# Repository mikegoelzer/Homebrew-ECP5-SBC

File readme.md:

# Homebrew RISC-V Computer

This is the hardware repo for a homebrew "personal computer" designed from scratch down to the logic gate level.

The computer is based on [my custom RISC-V CPU core](https://github.com/mikegoelzer/riscv) (pipelined, in-order, 5-stage) and has all the common peripherals you'd expect on a PC circa the early-2000s like USB, HDMI, keyboard and mouse, etc.

This repo is focused specifically on the PCBs necessary to build the complete computer.

## Hardware

In this repo, you'll find all the Kicad files and bills of materials needed to construct the entire computer.  There are several PCBs:

- [Compute Module](./hardware/cm/readme.md). This is the heart of the computer:  an FPGA that implements the RISC-V CPU and some SDRAM that serves as the computer's main memory. It has two 100-pin Hirose DF13 snap-in connectors on the bottom, which mate with the motherboard.
- [Motherboard](./hardware/motherboard/readme.md). The Compute Module snaps into this motherboard, which breaks out the common PC periperal interfaces, like HDMI, VGA, JTAG, and more.  It also has an SD card to serve as the computer's "hard drive," a boot flash, and some diagnostic LEDs and switches.
- [Power Supply](./hardware/pd-booster-16amps/readme.md). Power initially comes into the motherboard via a USB-C cable.  Because I wanted to learn a bit about USB Power Deliver (USB-PD) as part of this project, I designed this plug-in board that negotiates higher voltages and currents and then buck-boost converts them to a stable 5V to power the motherboard.
- [Hat](./hardware/hat/readme.md).  This is a top board that sits above the motherboard on standoffs and provides a touch screen plus a smaller OLED display for debugging your Verilog.  The name is, of course, inspired by the Pi HAT, though it bears no electrical or mechanical resemblance.

## About this project

This project was a personal hobby exercise that I pursued on and off over a couple of years.  Everything is massively over-engineered because I was trying to maximize my learnings. 🤷‍♀️

## Acknowledgements

This hardware was heavily inspired by the [ULX3S](https://radiona.org/ulx3s/), which I consider the best low-cost Lattice ECP5 FPGA board ever created.

I also borrowed ideas from several other open-source ECP5 designs:

- [Lattice ECP5 Eval Board](https://www.latticesemi.com/products/developmentboardsandkits/ecp5evaluationboard)
- [Trellis Board](https://github.com/gatecat/TrellisBoard).  Not sure if this was ever sold to the public, but this guy's design is utterly brilliant.
- [Orange Crab](https://github.com/orangecrab-fpga/orangecrab-hardware)

## License

This material is licensed under `CERN-OHL-S v2` (or later), a strong "copyleft" license. If you require more permissive terms or patent protection, please contact the author. A copy of the license can be found in the [LICENSES](./LICENSES) directory.

Copyright © 2025 Mike Goelzer <mike@goelzer.org>

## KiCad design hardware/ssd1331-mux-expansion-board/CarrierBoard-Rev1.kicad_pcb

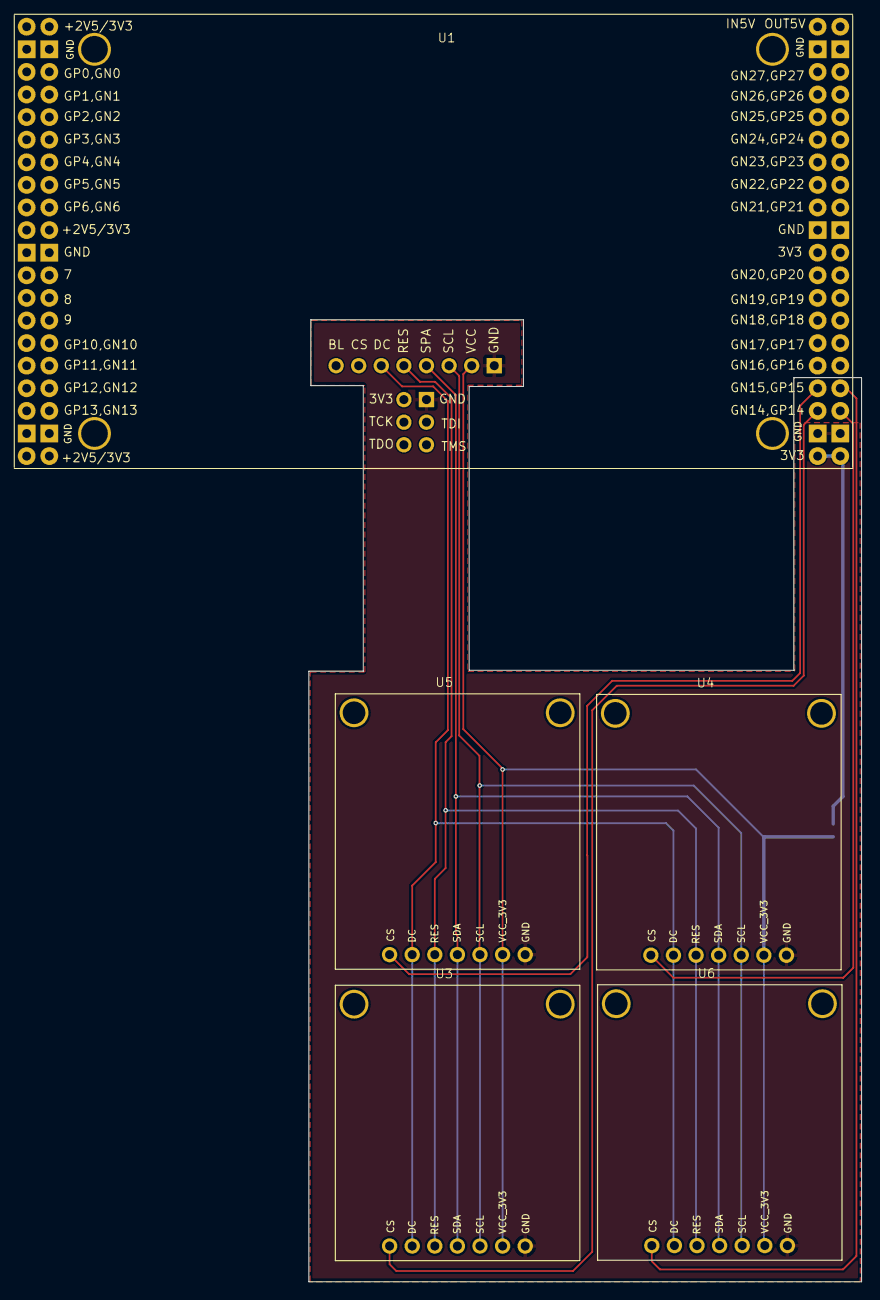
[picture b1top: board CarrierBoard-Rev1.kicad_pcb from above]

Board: 2 copper layers, 62.1 x 108.1 mm, 6 parts (1 on the bottom side), 11 nets.

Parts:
JP1: SolderJumper_2_Open; SolderJumper-2_P1.3mm_Open_TrianglePad1.0x1.5mm
U1: ULX3S
U3: OLED #3; OLED 0.95in 96x128 SPI_No_Bottom_Drill_Holes
U4: OLED #2; OLED 0.95in 96x128 SPI_No_Bottom_Drill_Holes
U5: OLED #1; OLED 0.95in 96x128 SPI_No_Bottom_Drill_Holes
U6: OLED #4; OLED 0.95in 96x128 SPI_No_Bottom_Drill_Holes

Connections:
GND: U1.3 (GND), U1.4 (GND), U1.21 (GND), U1.22 (GND), U1.37 (GND), U1.38 (GND), U1.43 (GND), U1.44 (GND), U1.59 (GND), U1.60 (GND), U1.77 (GND), U1.78 (GND), U1.88 (GND), U1.90 (GND), U3.7 (GND), U4.7 (GND), U5.7 (GND), U6.7 (GND)
unnamed: JP1.2 (B), U1.79 (3V3), U1.80 (3V3)
OLED_CS_1: U1.73 (GN15), U5.1 (CS)
OLED_CS_2: U1.76 (GP14), U4.1 (CS)
OLED_CS_3: U1.75 (GN14), U3.1 (CS)
OLED_CS_4: U1.74 (GP15), U6.1 (CS)
OLED_DC: U1.83 (OLED_DC), U3.2 (DC), U4.2 (DC), U5.2 (DC), U6.2 (DC)
OLED_MOSI: U1.85 (OLED_MOSI), U3.4 (SDA), U4.4 (SDA), U5.4 (SDA), U6.4 (SDA)
OLED_RST: U1.84 (OLED_RES), U3.3 (RES), U4.3 (RES), U5.3 (RES), U6.3 (RES)
OLED_SCK: U1.86 (OLED_SCK), U3.5 (SCL), U4.5 (SCL), U5.5 (SCL), U6.5 (SCL)
OLED_VCC: JP1.1 (A), U1.87 (OLED_VCC_3V3), U3.6 (VCC_3V3), U4.6 (VCC_3V3), U5.6 (VCC_3V3), U6.6 (VCC_3V3)

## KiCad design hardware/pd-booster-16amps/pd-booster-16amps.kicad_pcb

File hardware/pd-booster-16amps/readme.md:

# PD Booster (16 amps)

This is a USB-PD power supply that can deliver up to 16 amps at 5V.  It consists of two PCBs, which plug into each other:  a USB-PD controller and a buck-boost converter.

## Theory of Operation

USB-PD is mainly for battery charging, and the idea is that you have a USB-C cable coming into your device from a charger.  The charger initially supplies the standard 5V/2.5A, but you can negotiate over the CC lines side-channel to request both higher current and higher voltages (up to 20V).

Since you don't know in advance what voltage you will get, you need some additional circuitry to step down the voltage whatever you actually want to run at.  In my case, that's 5V.  The buck-boost converter is that additional circuitry:  it will maintain 5V output over the entire range of input voltages from 5V to as high as 20V.

## USB-PD Controller

The first PCB is the USB-PD controller, which is based on [TI TPS25730](https://www.ti.com/lit/ds/symlink/tps25730.pdf?ts=1707773923998&ref_url=https%253A%252F%252Fwww.mouser.at%252F).  It is resistor-strapped to request the highest voltage and current it can get (which would be 20V/5A), but will accept voltages as low as 5V.

## Buck-Boost Converter

The second PCB is the buck-boost converter.  It accepts whatever voltage the USB-PD controller was able to negotiate and regulates it to 5V.

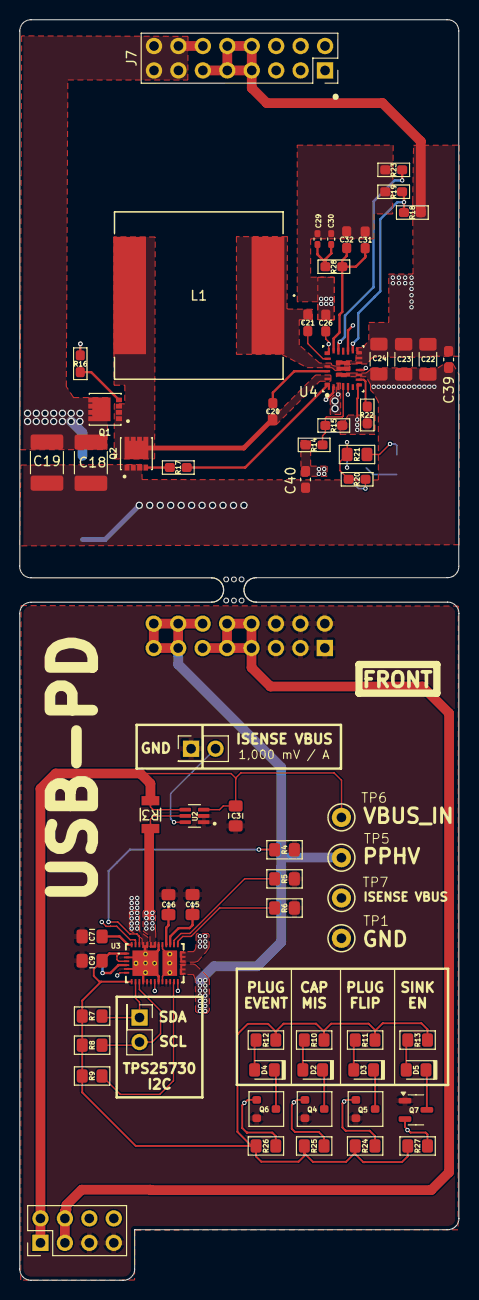
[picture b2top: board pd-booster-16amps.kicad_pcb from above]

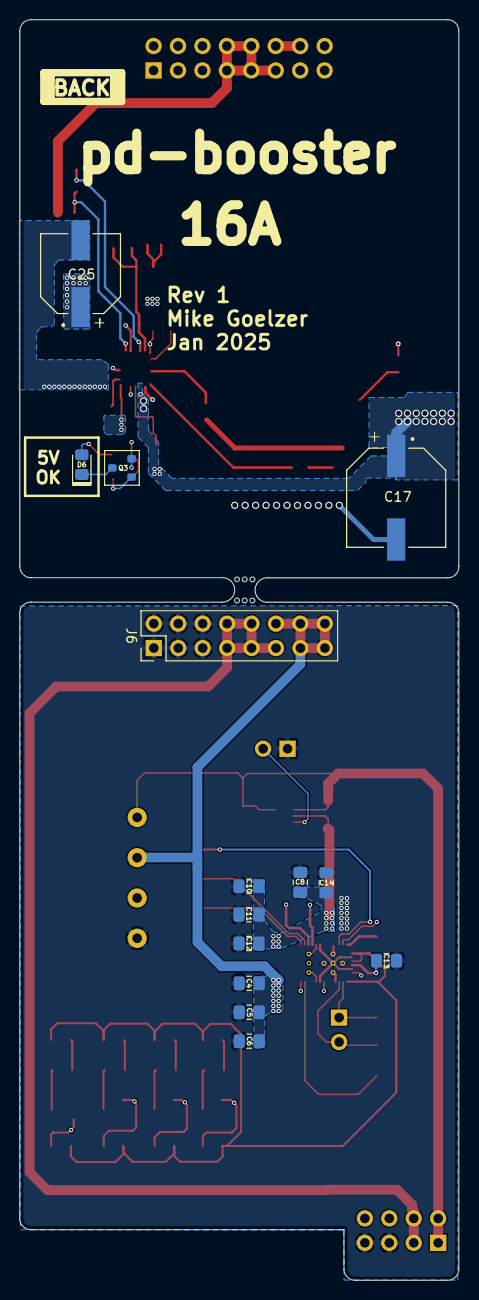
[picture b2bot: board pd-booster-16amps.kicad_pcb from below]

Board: 4 copper layers, 45.6 x 131.0 mm, 82 parts (14 on the bottom side), 48 nets.

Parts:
C3: 0.1uF; C_0805_2012Metric_Pad1.18x1.45mm_HandSolder
C4: 22uF/35V; C_0805_2012Metric_Pad1.18x1.45mm_HandSolder
C5, C6, C7, C9: 10uF/50V; C_0805_2012Metric_Pad1.18x1.45mm_HandSolder
C8, C10, C11, C12: 10nF/50V; C_0805_2012Metric_Pad1.18x1.45mm_HandSolder
C13, C14: 4.7uF/35V; C_0805_2012Metric_Pad1.18x1.45mm_HandSolder
C15, C16: 330pF/50V; C_0805_2012Metric_Pad1.18x1.45mm_HandSolder
C17: 330uF; CAP_25SVPF330M
C18, C19: 6.8uF; C_1812_4532Metric_Pad1.57x3.40mm_HandSolder
C20, C21: 100nF; C_0603_1608Metric_Pad1.08x0.95mm_HandSolder
C22, C23, C24: 100uF; C_1206_3216Metric_Pad1.33x1.80mm_HandSolder
C25: 560uF; CAP_16SVPF560M
C26: 4.7uF; C_0603_1608Metric_Pad1.08x0.95mm_HandSolder
C29, C30: 15nF; C_0402_1005Metric_Pad0.74x0.62mm_HandSolder
C31, C32: 10pF; C_0603_1608Metric_Pad1.08x0.95mm_HandSolder
C39, C40: 1uF; C_0603_1608Metric_Pad1.08x0.95mm_HandSolder
D2: Red; LED_0805_2012Metric_Pad1.15x1.40mm_HandSolder
D3: Yellow; LED_0805_2012Metric_Pad1.15x1.40mm_HandSolder
D4: Amber; LED_0805_2012Metric_Pad1.15x1.40mm_HandSolder
D5, D6: Green; LED_0805_2012Metric_Pad1.15x1.40mm_HandSolder
J2: 2x4 male 0.1"; PinHeader_2x04_P2.54mm_Vertical
J3, J5: PH1-02-UA; PinHeader_2x01_P2.54mm_Vertical
J6: female (front board); PinHeader_2x08_P2.54mm_Vertical
J7: male pins 16mm (back board); PinHeader_2x08_P2.54mm_Vertical
L1: 6.8uH; IND_IHLP-6767DZ_VIS-M
MB1: PCB mouse bites; mouse-bite-2.54mm-slot
Q1, Q2: CSD16327Q3; TRANS_CSD16327Q3
Q3, Q4, Q5, Q6: BSH111; SOT-23
Q7: BSS84 (PMOS); SOT-23-3
R3: 2mΩ 1% 1W; STA_CSNL1206_STP
R4, R5, R6, R9: 10k; R_0805_2012Metric_Pad1.15x1.40mm_HandSolder
R7, R8: 3.3k; R_0805_2012Metric_Pad1.15x1.40mm_HandSolder
R10, R11, R12, R13: 33k; R_0805_2012Metric_Pad1.15x1.40mm_HandSolder
R14: 226k; R_0603_1608Metric_Pad1.05x0.95mm_HandSolder
R15, R18: 100k; R_0603_1608Metric_Pad1.05x0.95mm_HandSolder
R16, R17: 1Ω; R_0603_1608Metric_Pad1.05x0.95mm_HandSolder
R19: 31.6k; R_0603_1608Metric_Pad1.05x0.95mm_HandSolder
R20: 102k; R_0603_1608Metric_Pad1.05x0.95mm_HandSolder
R21: 1k; R_0805_2012Metric_Pad1.15x1.40mm_HandSolder
R22: 50k; R_0603_1608Metric_Pad1.05x0.95mm_HandSolder
R23: 20.5k; R_0603_1608Metric_Pad1.05x0.95mm_HandSolder
R24, R25, R26, R27: 100k; R_0805_2012Metric_Pad1.15x1.40mm_HandSolder
R28: 11.3k; R_0603_1608Metric_Pad1.05x0.95mm_HandSolder
TP1: Black (GND); Keystone_Testpoint_5001_MWG
TP5: Red (PPHV); Keystone_Testpoint_5000_MWG
TP6: White (VBUS); Keystone_Testpoint_5002_MWG
TP7: Yellow (ISENSE VBUS); Keystone_Testpoint_5004_MWG
U2: INA211BIDCKT; SOT65P210X110-6N
U3: TPS25730; TPS25730DREFR
U4: TPS552882RPMR; RPM0026A-MFG

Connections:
/Buck-Boost/5V_OUT: C22.1, C23.1, C24.1, C25.1, C39.1, J2.3, J2.4, J6.7, J6.8, J6.9, J6.10, J6.11, J7.7, J7.8, J7.9, J7.10, J7.11, R18.2, U4.11 (VOUT), U4.12 (ISP), U4.13 (ISN), U4.26 (VOUT)
/Buck-Boost/5V_OUT_PG: Q3.1 (G), R20.2, U4.5 (PG)
/Buck-Boost/LDO_5V2: C26.1, R20.1, R21.2, U4.19 (VCC)
/Buck-Boost/SW1: C20.1, L1.2, Q1.1 (S), Q1.2 (S), Q1.3 (S), Q2.5-8 (D), U4.23 (SW1)
/Buck-Boost/SW2: C21.2, L1.1, U4.21 (SW2), U4.25 (SW2)
/Buck-Boost/V_MUX_OUT: C4.2, C5.2, C6.2, C17.1, C18.1, C19.1, C40.1, J6.12, J6.13, J6.14, J6.15, J6.16, J7.12, J7.13, J7.14, J7.15, J7.16, Q1.5-8 (D), R14.2, TP5.1, U3.20 (PPHV_1), U3.21 (PPHV_2), U3.22 (PPHV_3), U3.41 (PPHV_4), U4.3 (VIN)
/Connectors/VBUS_IN: C3.1, J2.1, J2.2, R3.1, TP6.1, U2.3 (V+), U2.4 (+IN)
/USB PD/ADCIN2: C9.2, R7.1, R8.1, R9.1, R10.2, R11.2, R12.2, R13.2, R24.1, R25.1, R26.1, R27.1, U3.1 (LDO_3V3), U3.3 (ADCIN2), U3.7 (ADCIN4)
/USB PD/CAP_MIS: Q4.1 (G), R25.2, U3.6 (CAP_MIS)
/USB PD/DRAIN: U3.15 (DRAIN_1), U3.30 (DRAIN_2), U3.40 (DRAIN_3)
/USB PD/LDO_1V5: C13.2, U3.4 (LDO_1V5)
/USB PD/PLUG_EVENT: Q6.1 (G), R26.2, U3.37 (PLUG_EVENT)
/USB PD/PLUG_FLIP: Q5.1 (G), R24.2, U3.13 (PLUG_FLIP)
/USB PD/VBUS_IN_POST_SHUNT: C8.2, C10.2, C11.2, C12.2, C14.2, R3.2, U2.5 (-IN), U3.23 (VBUS_IN_1), U3.24 (VBUS_IN_2), U3.25 (VBUS_IN_3), U3.32 (VBUS_1), U3.33 (VBUS_2), U3.42 (VBUS_IN_4), U3.43 (VBUS_3)
/USB PD/VIN_3V3: C7.2, U3.38 (VIN_3V3)
/USB PD/~FAULT_IN: R9.2, U3.18 (~FAULT_IN)
/USB PD/~SINK_EN: Q7.2 (G), R27.2, U3.19 (~SINK_EN)
CC1: C15.2, J2.6, U3.28 (CC1)
CC2: C16.2, J2.8, U3.29 (CC2)
GND: C3.2, C4.1, C5.1, C6.1, C7.1, C8.1, C9.1, C10.1, C11.1, C12.1, C13.1, C14.1, C15.1, C16.1, C17.2, C18.2, C19.2, C22.2, C23.2, C24.2, C25.2, C26.2, C29.2, C30.2, C31.2, C32.2, C39.2, C40.2, J2.5, J2.7, J3.1, J6.1, J6.2, J6.3, J6.4, J6.5, J6.6, J7.1, J7.2, J7.3, J7.4, J7.5, J7.6, Q2.1 (S), Q2.2 (S), Q2.3 (S), Q3.2 (S), Q4.2 (S), Q5.2 (S), Q6.2 (S), Q7.1 (D), R4.2, R5.2, R6.2, R15.1, R19.1, R22.1, R23.1, TP1.1, U2.1 (REF), U2.2 (GND), U3.2 (ADCIN1), U3.5 (ADCIN3), U3.10 (DBG_ACC), U3.11 (GND_1), U3.12 (GND_2), U3.14 (GND_3), U3.16 (GND_4), U3.17 (GND_5), U3.31 (GND_6), U3.34 (GND_7), U3.35 (GND_8), U3.39 (GND_9), U3.44 (GND_10), U4.7 (DITH_SYNC), U4.9 (PGND), U4.10 (AGND), U4.15 (MODE), U4.24 (PGND)
ISENSE_VBUS: J3.2, TP7.1, U2.6 (OUT)
unnamed: C29.1, C30.1, R28.1
unnamed: D2.2 (A), R10.1
unnamed: D2.1 (K), Q4.3 (D)
unnamed: D3.2 (A), R11.1
unnamed: D3.1 (K), Q5.3 (D)
unnamed: D4.2 (A), R12.1
unnamed: D4.1 (K), Q6.3 (D)
unnamed: D5.2 (A), R13.1
unnamed: D5.1 (K), Q7.3 (S)
unnamed: D6.2 (A), R21.1
unnamed: D6.1 (K), Q3.3 (D)
unnamed: Q1.4 (G), R16.2
unnamed: Q2.4 (G), R17.2
unnamed: R6.1, U3.26 (RESERVED_1)
unnamed: R5.1, U3.27 (RESERVED_2)
unnamed: R4.1, U3.36 (RESERVED_3)
unnamed: C20.2, U4.22 (BOOT1)
unnamed: C21.1, U4.20 (BOOT2)
unnamed: C31.1, C32.1, R28.2, U4.18 (COMP)
unnamed: R16.1, U4.2 (DR1H)
unnamed: R17.1, U4.1 (DR1L)
unnamed: R14.1, R15.2, U4.4 (EN)
unnamed: R18.1, R19.2, U4.14 (FB)
unnamed: R22.2, U4.8 (FSW)
unnamed: R23.2, U4.17 (ILIM)
TPS25730_I2C_SCL: J5.2, R8.2, U3.9 (I2CT_SCL)
TPS25730_I2C_SDA: J5.1, R7.2, U3.8 (I2CT_SDA)

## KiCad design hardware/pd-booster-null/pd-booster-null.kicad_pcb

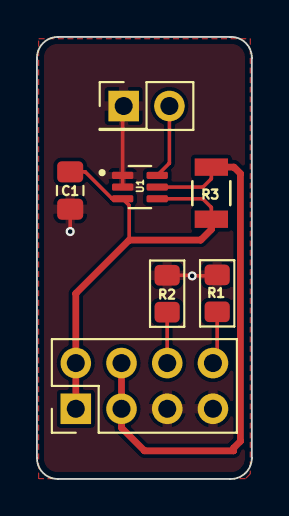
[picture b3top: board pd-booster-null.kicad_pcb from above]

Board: 2 copper layers, 11.9 x 24.6 mm, 7 parts (0 on the bottom side), 6 nets.

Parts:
C1: 0.1uF; C_0805_2012Metric_Pad1.18x1.45mm_HandSolder
J1: 2x4 male 0.1"; PinHeader_2x04_P2.54mm_Vertical
J2: PH1RB-02-UA; PinHeader_2x01_P2.54mm_Vertical
R1, R2: 5.1k 1%; R_0805_2012Metric_Pad1.15x1.40mm_HandSolder
R3: 2mΩ 1% 1W; STA_CSNL1206_STP
U1: INA211BIDCKT; SOT65P210X110-6N

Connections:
/Pass-Thru/5V_OUT: J1.3, J1.4, R3.2, U1.5 (-IN)
/Pass-Thru/CC1: J1.6, R2.1
/Pass-Thru/CC2: J1.8, R1.1
/Pass-Thru/ISENSE: J2.2, U1.6 (OUT)
/Pass-Thru/VBUS_IN: C1.1, J1.1, J1.2, R3.1, U1.3 (V+), U1.4 (+IN)
GND: C1.2, J1.5, J1.7, J2.1, R1.2, R2.2, U1.1 (REF), U1.2 (GND)

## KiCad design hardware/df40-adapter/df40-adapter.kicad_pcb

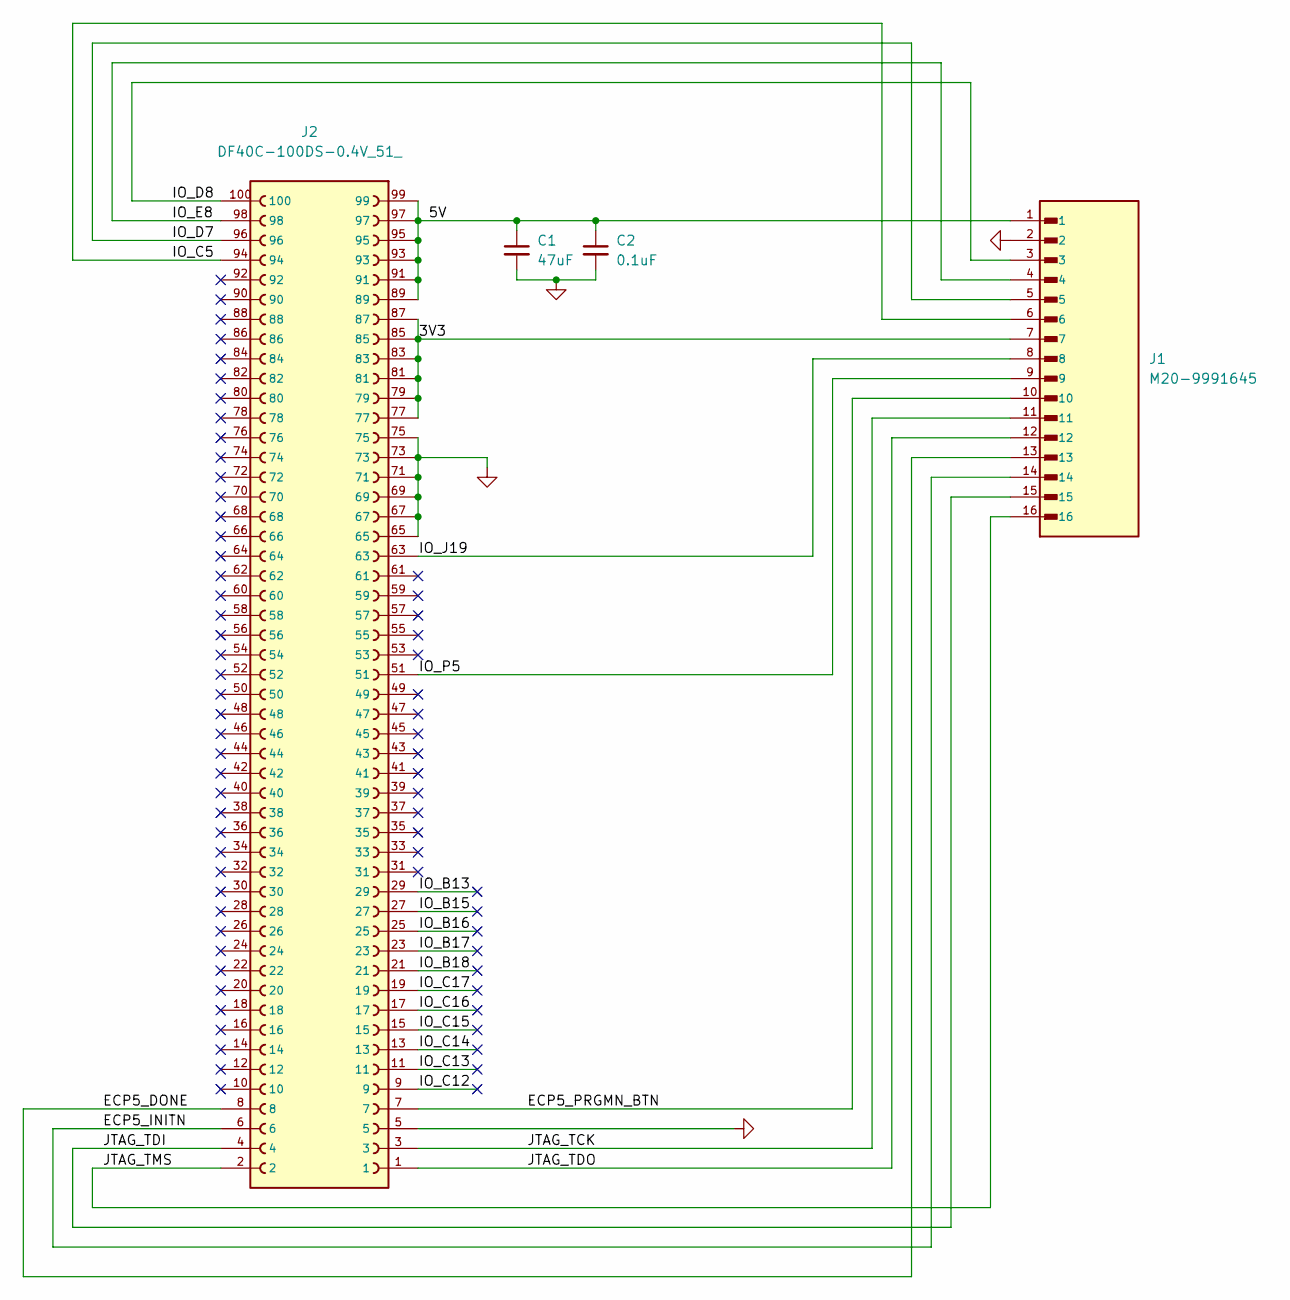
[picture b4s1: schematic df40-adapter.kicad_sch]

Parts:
C1: 47uF; C_0805_2012Metric_Pad1.18x1.45mm_HandSolder; MPN GRM21BR61A476ME15L
C2: 0.1uF; C_0805_2012Metric_Pad1.18x1.45mm_HandSolder; MPN CC0805KRX7R9BB104
J1: M20-9991645; HARWIN_M20-9991645; MPN M20-9991645
J2: DF40C-100DS-0.4V_51_; HIROSE_DF40C-100DS-0.4V_51_; PARTREV Oct.1.2023

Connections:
/3V3: J1.7, J2.77, J2.79, J2.81, J2.83, J2.85, J2.87
/5V: C1.1, C2.1, J1.1, J2.89, J2.91, J2.93, J2.95, J2.97, J2.99
/ECP5_DONE: J1.13, J2.8
/ECP5_INITN: J1.14, J2.6
/ECP5_PRGMN_BTN: J1.10, J2.7
/IO_B13: J2.29
/IO_B15: J2.27
/IO_B16: J2.25
/IO_B17: J2.23
/IO_B18: J2.21
/IO_C5: J1.6, J2.94
/IO_C12: J2.9
/IO_C13: J2.11
/IO_C14: J2.13
/IO_C15: J2.15
/IO_C16: J2.17
/IO_C17: J2.19
/IO_D7: J1.5, J2.96
/IO_D8: J1.3, J2.100
/IO_E8: J1.4, J2.98
/IO_J19: J1.8, J2.63
/IO_P5: J1.9, J2.51
/JTAG_TCK: J1.11, J2.3
/JTAG_TDI: J1.15, J2.4
/JTAG_TDO: J1.12, J2.1
/JTAG_TMS: J1.16, J2.2
GND: C1.2, C2.2, J1.2, J2.5, J2.65, J2.67, J2.69, J2.71, J2.73, J2.75

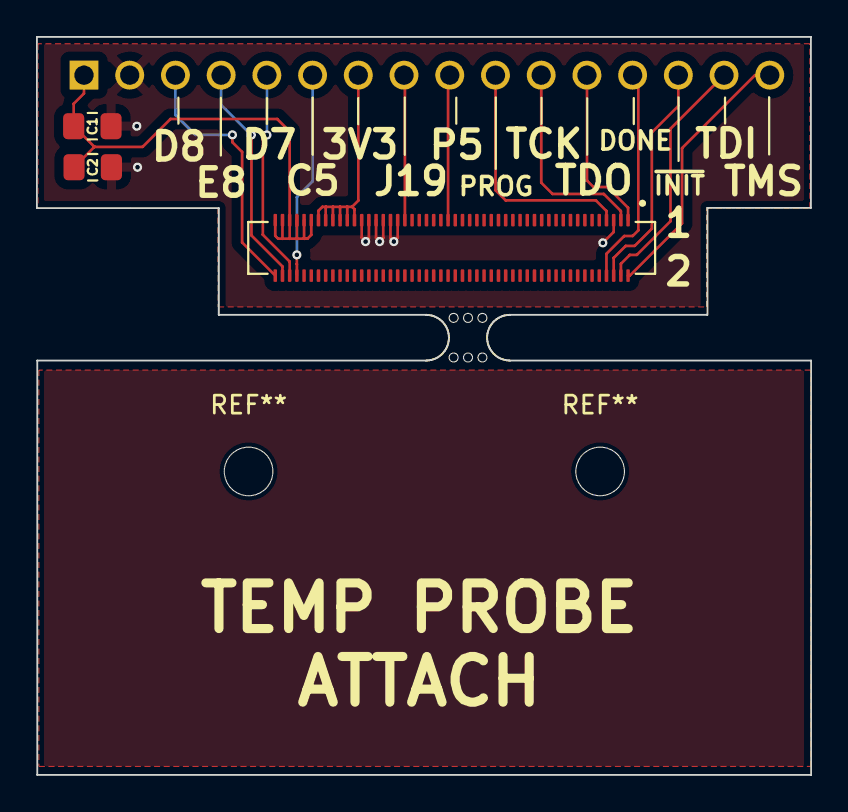
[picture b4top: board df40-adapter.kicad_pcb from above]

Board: 2 copper layers, 43.0 x 41.0 mm, 5 parts (1 on the bottom side), 16 nets.

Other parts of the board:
mouse-bite-2.54mm-slot: VAL**; mouse-bite-2.54mm-slot

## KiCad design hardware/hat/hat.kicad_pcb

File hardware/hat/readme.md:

# Hat

This is the top board that sits above the motherboard on standoffs and provides a touch screen plus a smaller OLED display for debugging the CPU's Verilog.

## OLED

The OLED is an 0.95" (96x64) SSD1331 display.  It is controlled via SPI entirely in Verilog.  I use it for very low-level debugging of the CPU itself, e.g., to display a register value or dump the contents of memory.

## Touch Screen

The touch screen is [this cool 2.8" 240x320 TFT LCD from Adafruit](https://www.adafruit.com/product/2090).  It is intended to be under software control rather than at the Verilog level.

## Power

Power is provided by the flat-flexible cable coming from the motherboard.  It is the same 5V supply as the motherboard itself.

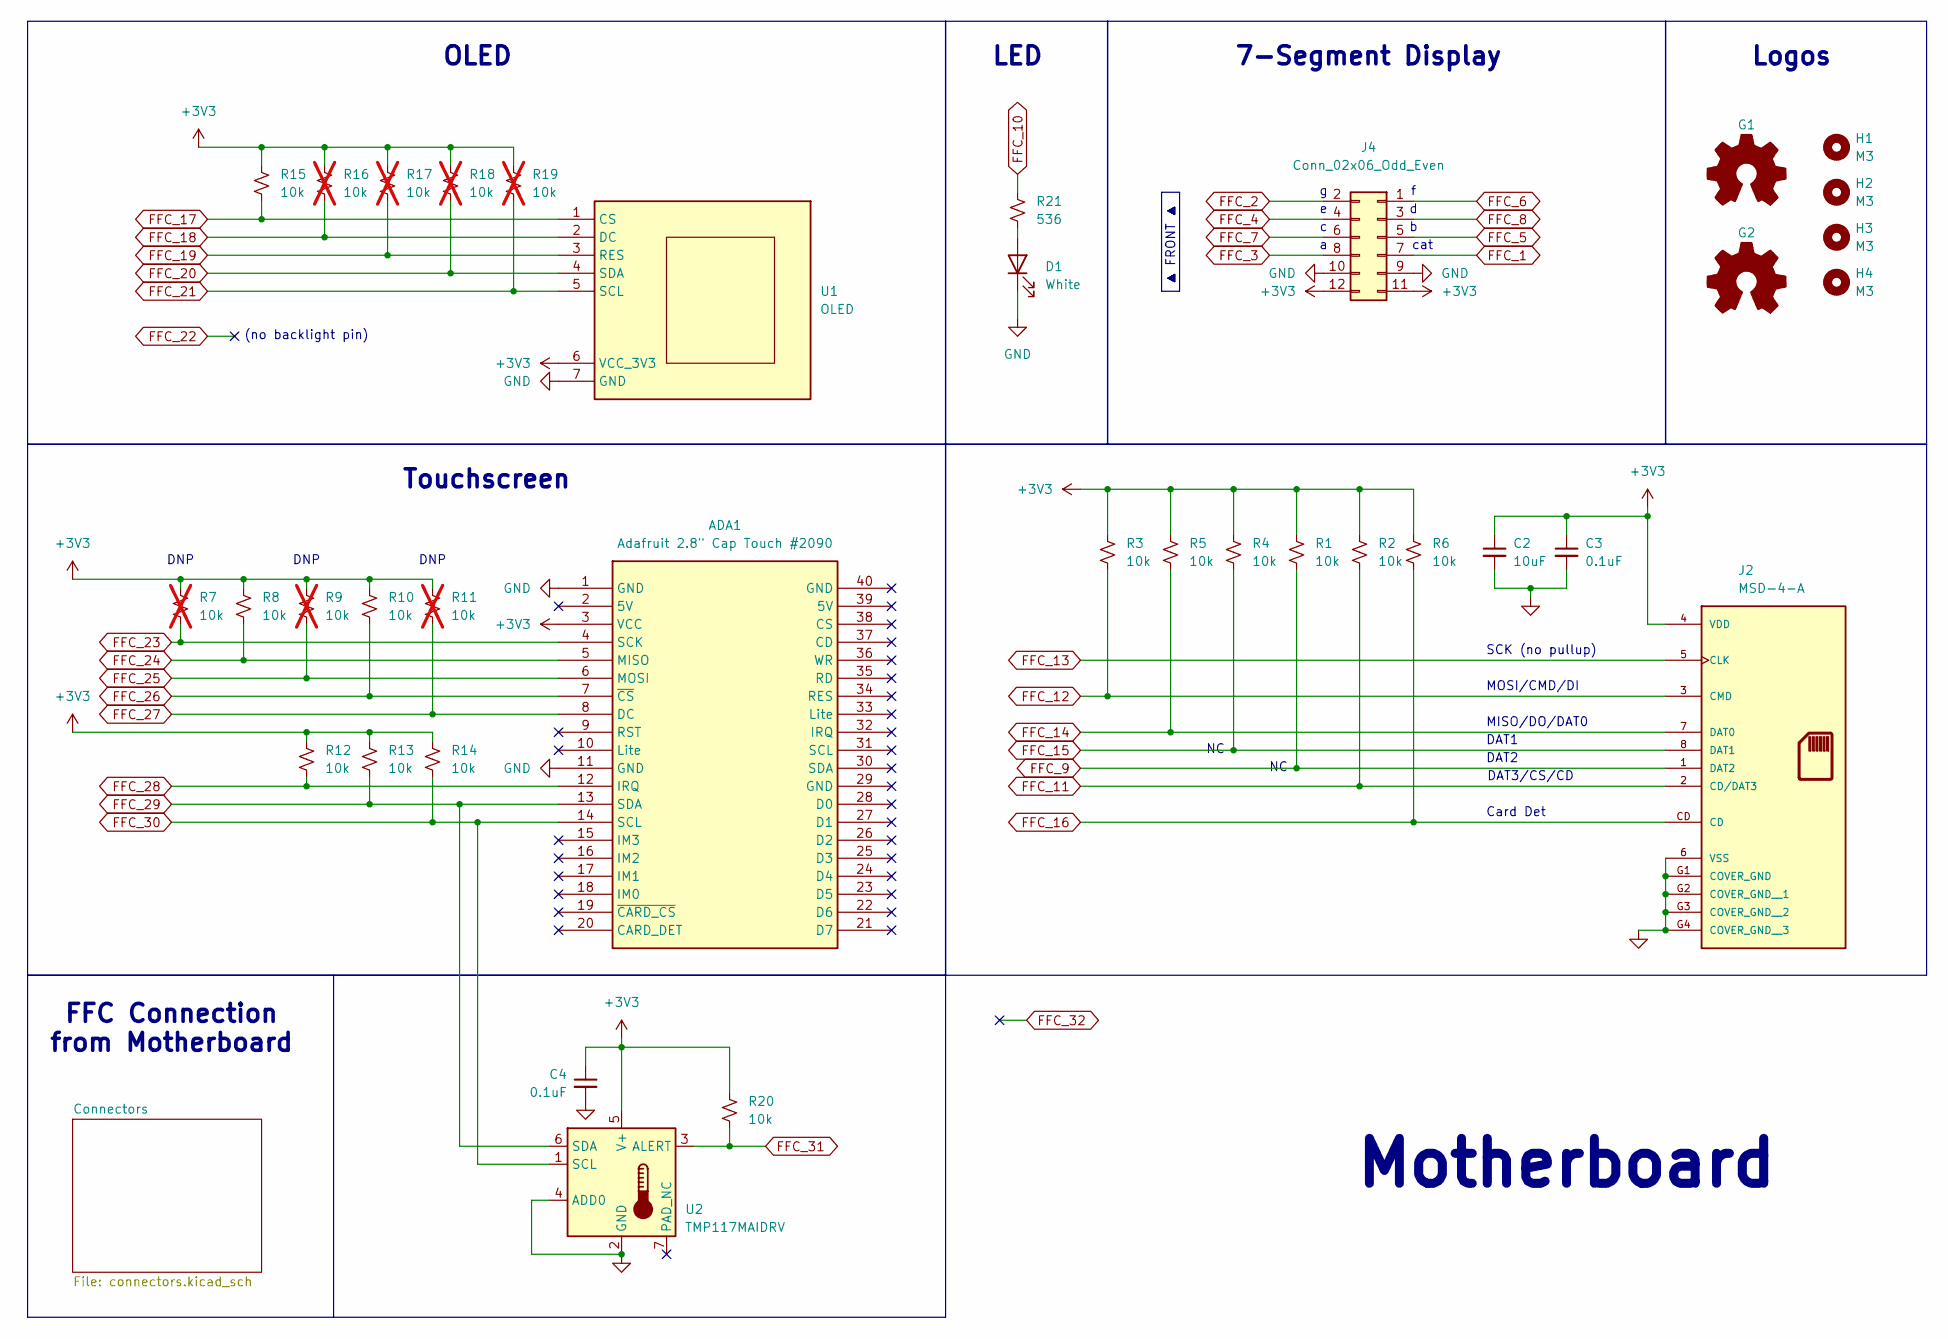
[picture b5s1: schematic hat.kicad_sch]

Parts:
ADA1: Adafruit 2.8" Cap Touch #2090; Adafruit 2.8 Cap Touchscreen (2090)
C2: 10uF; C_0603_1608Metric_Pad1.08x0.95mm_HandSolder; MPN GRM188R60J106ME47D
C3, C4: 0.1uF; C_0603_1608Metric_Pad1.08x0.95mm_HandSolder; MPN CC0603KRX7R7BB104
D1: White; QBLP631_White_LED_0805; MPN QBLP631-IW5
G1: Logo_Open_Hardware_Small; KiCad-Logo2_5mm_SilkScreen
G2: Logo_Open_Hardware_Small; OSHW-Logo2_14.6x12mm_SilkScreen
H1, H2, H3, H4: M3; MountingHole_3.2mm_M3; MPN 97790603111
J2: MSD-4-A; CUI_MSD-4-A; PARTREV 1.0
J4: Conn_02x06_Odd_Even; PinSocket_2x06_P2.54mm_Vertical
R1, R2, R3, R4, R5, R6, R8, R10, R12, R13, R14, R15, R20: 10k; R_0603_1608Metric_Pad1.05x0.95mm_HandSolder; MPN RC0603FR-0710KL
R7, R9, R11, R16, R17, R18, R19: 10k; R_0603_1608Metric_Pad1.05x0.95mm_HandSolder; MPN RC0603FR-0710KL; not fitted
R21: 536; R_0805_2012Metric_Pad1.15x1.40mm; MPN RC0805FR-07536RL
U1: OLED; OLED_0.95in_96x128_SPI_No_Bottom_Drill_Holes; MPN N/A
U2: TMP117MAIDRV; WSON-6-1EP_2x2mm_P0.65mm_EP1x1.6mm; MPN TMP117MAIDRVR

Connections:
+3V3: ADA1.3 (VCC), C2.1, C3.1, C4.1, J2.4 (VDD), J4.11, J4.12, R1.1, R2.1, R3.1, R4.1, R5.1, R6.1, R7.1, R8.1, R9.1, R10.1, R11.1, R12.1, R13.1, R14.1, R15.1, R16.1, R17.1, R18.1, R19.1, R20.1, U1.6 (VCC_3V3), U2.5 (V+); also elsewhere on the board
FFC_1: J4.7; also elsewhere on the board
FFC_2: J4.2; also elsewhere on the board
FFC_3: J4.8; also elsewhere on the board
FFC_4: J4.4; also elsewhere on the board
FFC_5: J4.5; also elsewhere on the board
FFC_6: J4.1; also elsewhere on the board
FFC_7: J4.6; also elsewhere on the board
FFC_8: J4.3; also elsewhere on the board
FFC_9: J2.1 (DAT2), R1.2; also elsewhere on the board
FFC_10: R21.1; also elsewhere on the board
FFC_11: J2.2 (CD/DAT3), R2.2; also elsewhere on the board
FFC_12: J2.3 (CMD), R3.2; also elsewhere on the board
FFC_13: J2.5 (CLK); also elsewhere on the board
FFC_14: J2.7 (DAT0), R5.2; also elsewhere on the board
FFC_15: J2.8 (DAT1), R4.2; also elsewhere on the board
FFC_16: J2.CD, R6.2; also elsewhere on the board
FFC_17: R15.2, U1.1 (CS); also elsewhere on the board
FFC_18: R16.2, U1.2 (DC); also elsewhere on the board
FFC_19: R17.2, U1.3 (RES); also elsewhere on the board
FFC_20: R18.2, U1.4 (SDA); also elsewhere on the board
FFC_21: R19.2, U1.5 (SCL); also elsewhere on the board
FFC_23: ADA1.4 (SCK), R7.2; also elsewhere on the board
FFC_24: ADA1.5 (MISO), R8.2; also elsewhere on the board
FFC_25: ADA1.6 (MOSI), R9.2; also elsewhere on the board
FFC_26: ADA1.7 (~CS), R10.2; also elsewhere on the board
FFC_27: ADA1.8 (DC), R11.2; also elsewhere on the board
FFC_28: ADA1.12 (IRQ), R12.2; also elsewhere on the board
FFC_29: ADA1.13 (SDA), R13.2, U2.6 (SDA); also elsewhere on the board
FFC_30: ADA1.14 (SCL), R14.2, U2.1 (SCL); also elsewhere on the board
FFC_31: R20.2, U2.3 (ALERT); also elsewhere on the board
GND: ADA1.1 (GND), ADA1.11 (GND), C2.2, C3.2, C4.2, D1.2 (K), J2.6 (VSS), J2.G1 (COVER_GND), J2.G2 (COVER_GND__1), J2.G3 (COVER_GND__2), J2.G4 (COVER_GND__3), J4.9, J4.10, U1.7 (GND), U2.2 (GND), U2.4 (ADD0); also elsewhere on the board
unnamed: D1.1 (A), R21.2

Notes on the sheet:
DNP
Logos
FFC Connection from Motherboard
MOSI/CMD/DI
7-Segment Display
LED
DAT2
Touchscreen
DAT1
▲ FRONT ▲
MISO/DO/DAT0
SCK (no pullup)
DAT3/CS/CD
Card Det
cat
Motherboard
OLED
(no backlight pin)

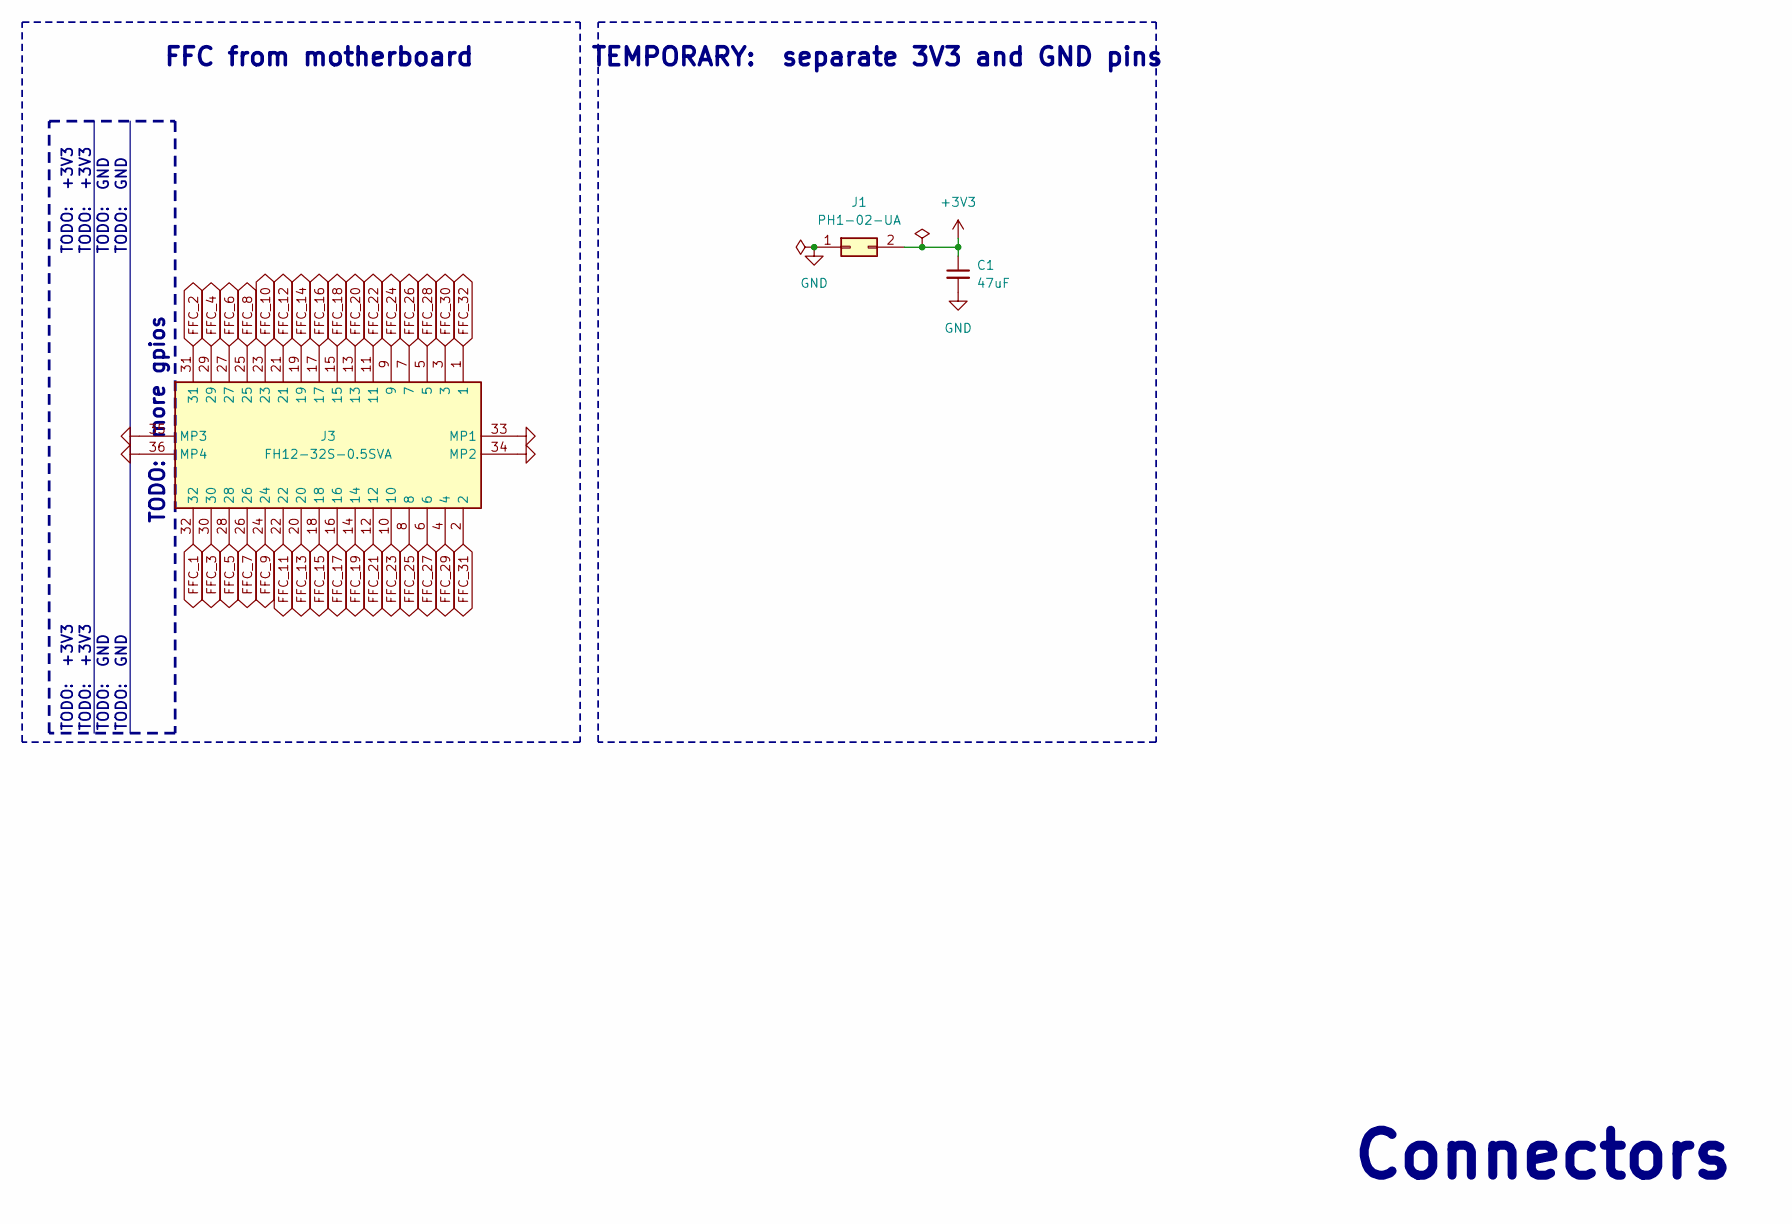
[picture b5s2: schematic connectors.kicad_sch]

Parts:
C1: 47uF; C_0603_1608Metric_Pad1.08x0.95mm_HandSolder; MPN GRM188R60J476ME15D
J1: PH1-02-UA; PinHeader_2x01_P2.54mm_Vertical; MPN PH1-02-UA
J3: FH12-32S-0.5SVA; FH1232S05SVA54; Mouser Part Number 798-FH1232S0.5SVA54

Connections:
+3V3: C1.1, J1.2; also elsewhere on the board
FFC_1: J3.32; also elsewhere on the board
FFC_2: J3.31; also elsewhere on the board
FFC_3: J3.30; also elsewhere on the board
FFC_4: J3.29; also elsewhere on the board
FFC_5: J3.28; also elsewhere on the board
FFC_6: J3.27; also elsewhere on the board
FFC_7: J3.26; also elsewhere on the board
FFC_8: J3.25; also elsewhere on the board
FFC_9: J3.24; also elsewhere on the board
FFC_10: J3.23; also elsewhere on the board
FFC_11: J3.22; also elsewhere on the board
FFC_12: J3.21; also elsewhere on the board
FFC_13: J3.20; also elsewhere on the board
FFC_14: J3.19; also elsewhere on the board
FFC_15: J3.18; also elsewhere on the board
FFC_16: J3.17; also elsewhere on the board
FFC_17: J3.16; also elsewhere on the board
FFC_18: J3.15; also elsewhere on the board
FFC_19: J3.14; also elsewhere on the board
FFC_20: J3.13; also elsewhere on the board
FFC_21: J3.12; also elsewhere on the board
FFC_22: J3.11
FFC_23: J3.10; also elsewhere on the board
FFC_24: J3.9; also elsewhere on the board
FFC_25: J3.8; also elsewhere on the board
FFC_26: J3.7; also elsewhere on the board
FFC_27: J3.6; also elsewhere on the board
FFC_28: J3.5; also elsewhere on the board
FFC_29: J3.4; also elsewhere on the board
FFC_30: J3.3; also elsewhere on the board
FFC_31: J3.2; also elsewhere on the board
FFC_32: J3.1
GND: C1.2, J1.1, J3.33 (MP1), J3.34 (MP2), J3.35 (MP3), J3.36 (MP4); also elsewhere on the board

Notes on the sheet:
FFC from motherboard
TODO: GND
TODO: +3V3
TEMPORARY: separate 3V3 and GND pins
TODO: more gpios
Connectors

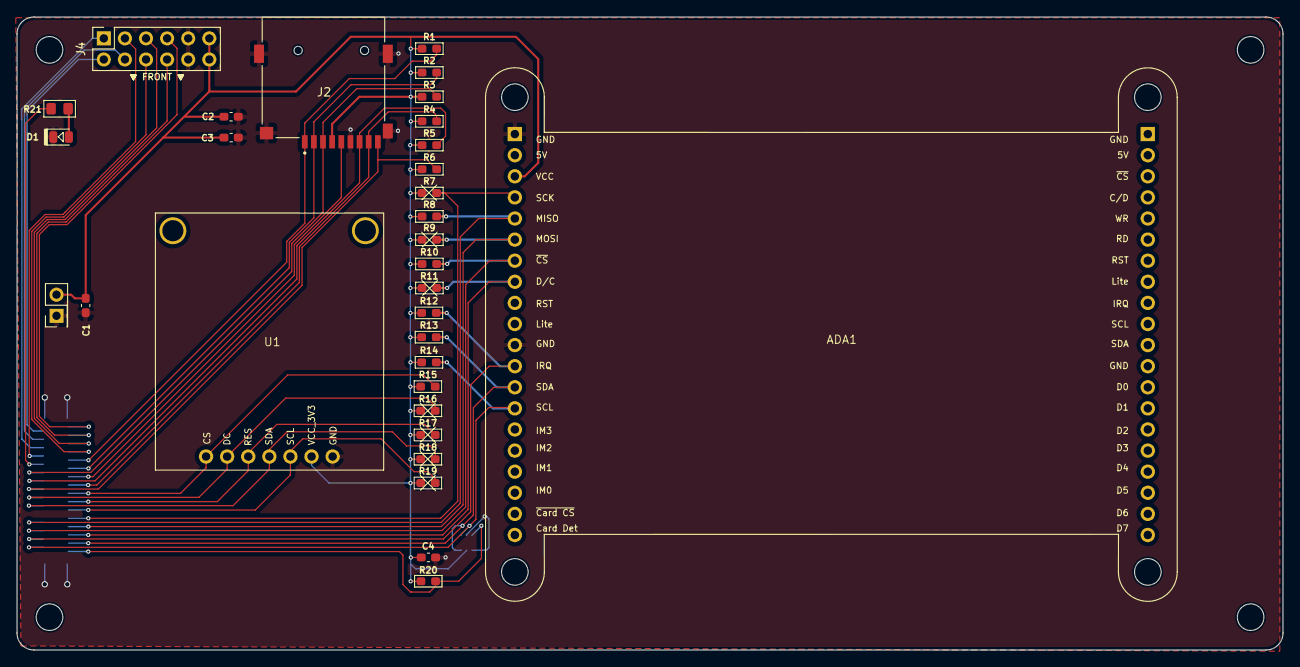
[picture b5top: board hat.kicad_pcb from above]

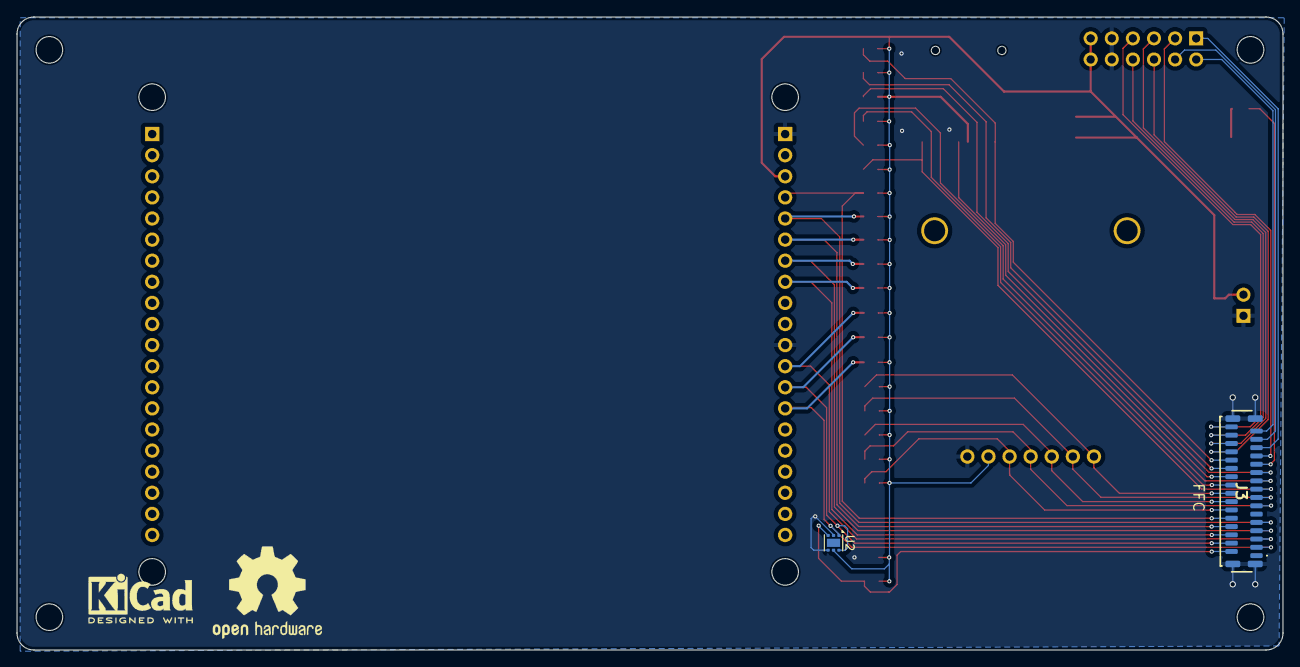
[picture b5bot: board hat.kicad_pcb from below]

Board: 2 copper layers, 152.4 x 76.2 mm, 39 parts (4 on the bottom side), 33 nets.
